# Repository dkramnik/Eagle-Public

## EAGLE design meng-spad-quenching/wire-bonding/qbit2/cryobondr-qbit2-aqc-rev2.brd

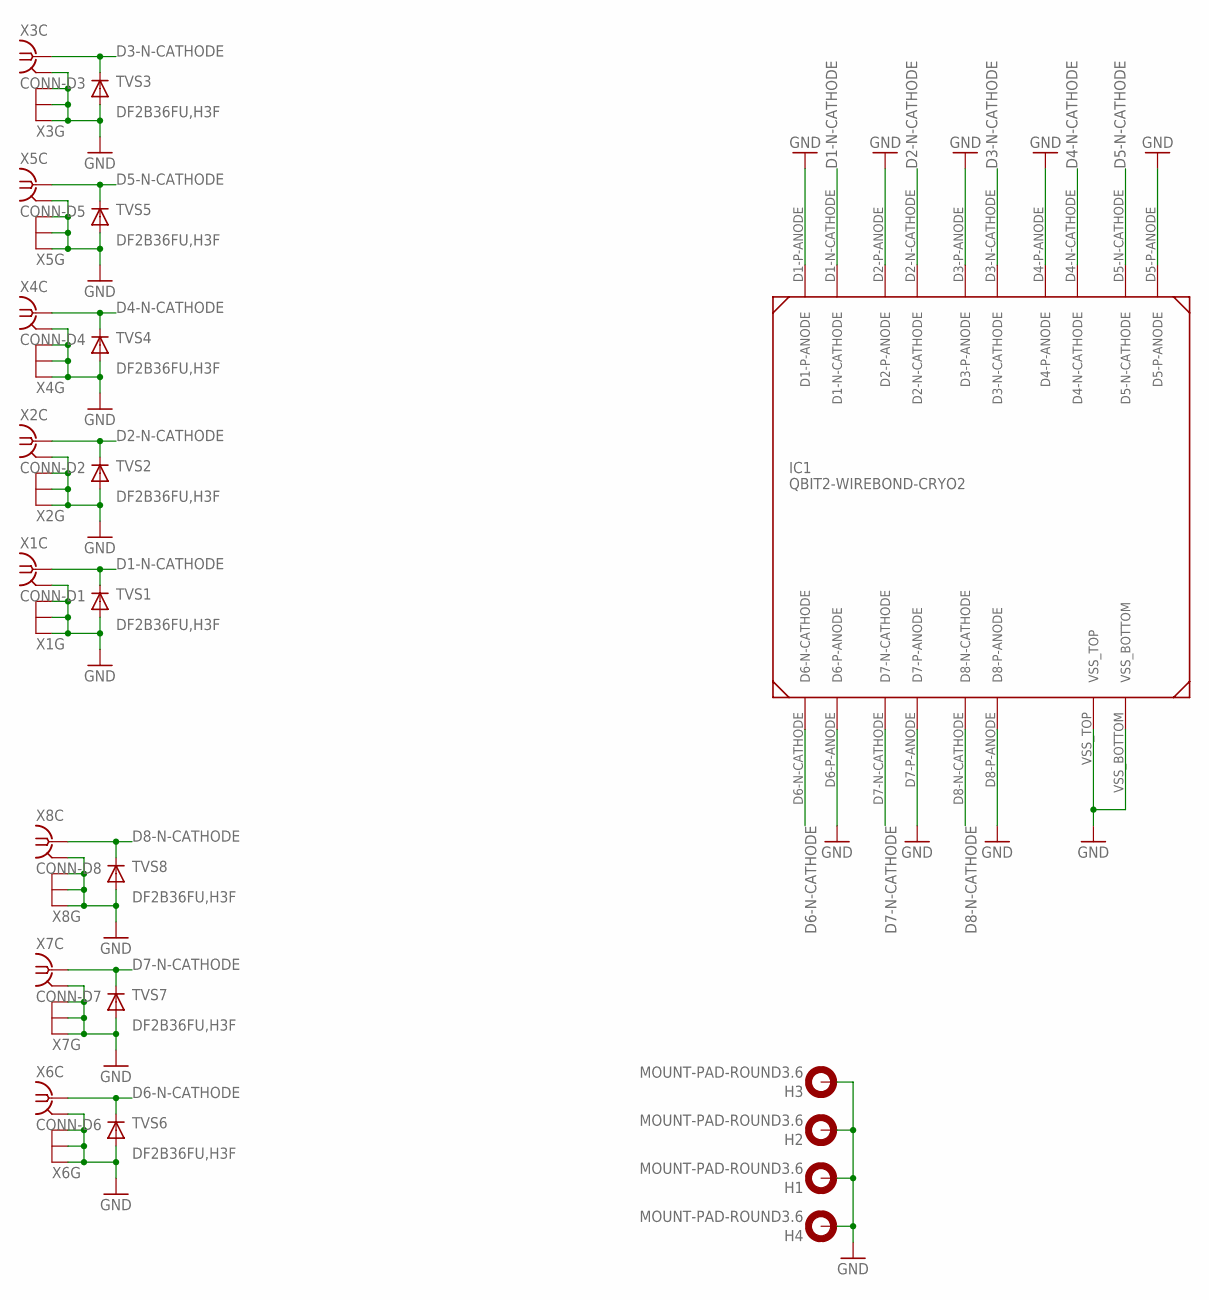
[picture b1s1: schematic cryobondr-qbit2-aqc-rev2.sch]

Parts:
H1, H2, H3, H4: MOUNT-PAD-ROUND3.6; 3,6-PAD
IC1: QBIT2-WIREBOND-CRYO2
TVS1, TVS2, TVS3, TVS4, TVS5, TVS6, TVS7, TVS8: DF2B36FU,H3F; SOD323-R
X1: CONN-D1; MMCX-SMT-BIGPADS
X2: CONN-D2; MMCX-SMT-BIGPADS
X3: CONN-D3; MMCX-SMT-BIGPADS
X4: CONN-D4; MMCX-SMT-BIGPADS
X5: CONN-D5; MMCX-SMT-BIGPADS
X6: CONN-D6; MMCX-SMT-BIGPADS
X7: CONN-D7; MMCX-SMT-BIGPADS
X8: CONN-D8; MMCX-SMT-BIGPADS

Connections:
D1-N-CATHODE: IC1.D1-N-CATHODE, TVS1.C, X1.S (1)
D2-N-CATHODE: IC1.D2-N-CATHODE, TVS2.C, X2.S (1)
D3-N-CATHODE: IC1.D3-N-CATHODE, TVS3.C, X3.S (1)
D4-N-CATHODE: IC1.D4-N-CATHODE, TVS4.C, X4.S (1)
D5-N-CATHODE: IC1.D5-N-CATHODE, TVS5.C, X5.S (1)
D6-N-CATHODE: IC1.D6-N-CATHODE, TVS6.C, X6.S (1)
D7-N-CATHODE: IC1.D7-N-CATHODE, TVS7.C, X7.S (1)
D8-N-CATHODE: IC1.D8-N-CATHODE, TVS8.C, X8.S (1)
GND: H1.B3,6, H2.B3,6, H3.B3,6, H4.B3,6, IC1.D1-P-ANODE, IC1.D2-P-ANODE, IC1.D3-P-ANODE, IC1.D4-P-ANODE, IC1.D5-P-ANODE, IC1.D6-P-ANODE, IC1.D7-P-ANODE, IC1.D8-P-ANODE, IC1.VSS_BOTTOM, IC1.VSS_TOP, TVS1.A, TVS2.A, TVS3.A, TVS4.A, TVS5.A, TVS6.A, TVS7.A, TVS8.A, X1.G1 (GND), X1.G2 (GND), X1.G3 (GND), X1.G4 (GND), X2.G1 (GND), X2.G2 (GND), X2.G3 (GND), X2.G4 (GND), X3.G1 (GND), X3.G2 (GND), X3.G3 (GND), X3.G4 (GND), X4.G1 (GND), X4.G2 (GND), X4.G3 (GND), X4.G4 (GND), X5.G1 (GND), X5.G2 (GND), X5.G3 (GND), X5.G4 (GND), X6.G1 (GND), X6.G2 (GND), X6.G3 (GND), X6.G4 (GND), X7.G1 (GND), X7.G2 (GND), X7.G3 (GND), X7.G4 (GND), X8.G1 (GND), X8.G2 (GND), X8.G3 (GND), X8.G4 (GND)

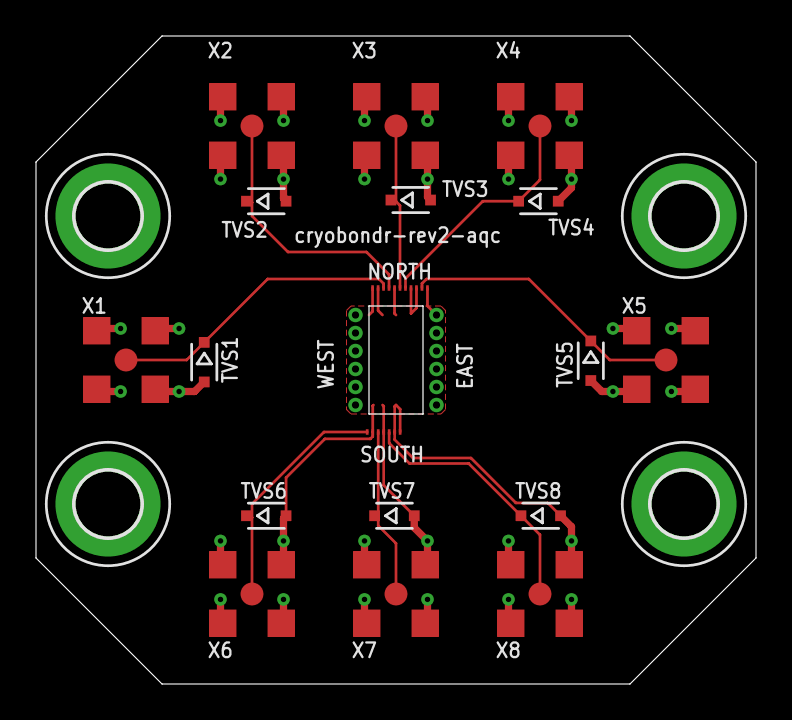
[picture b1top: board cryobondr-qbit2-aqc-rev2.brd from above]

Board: 2 copper layers, 40.0 x 36.0 mm, 21 parts (0 on the bottom side), 9 nets.

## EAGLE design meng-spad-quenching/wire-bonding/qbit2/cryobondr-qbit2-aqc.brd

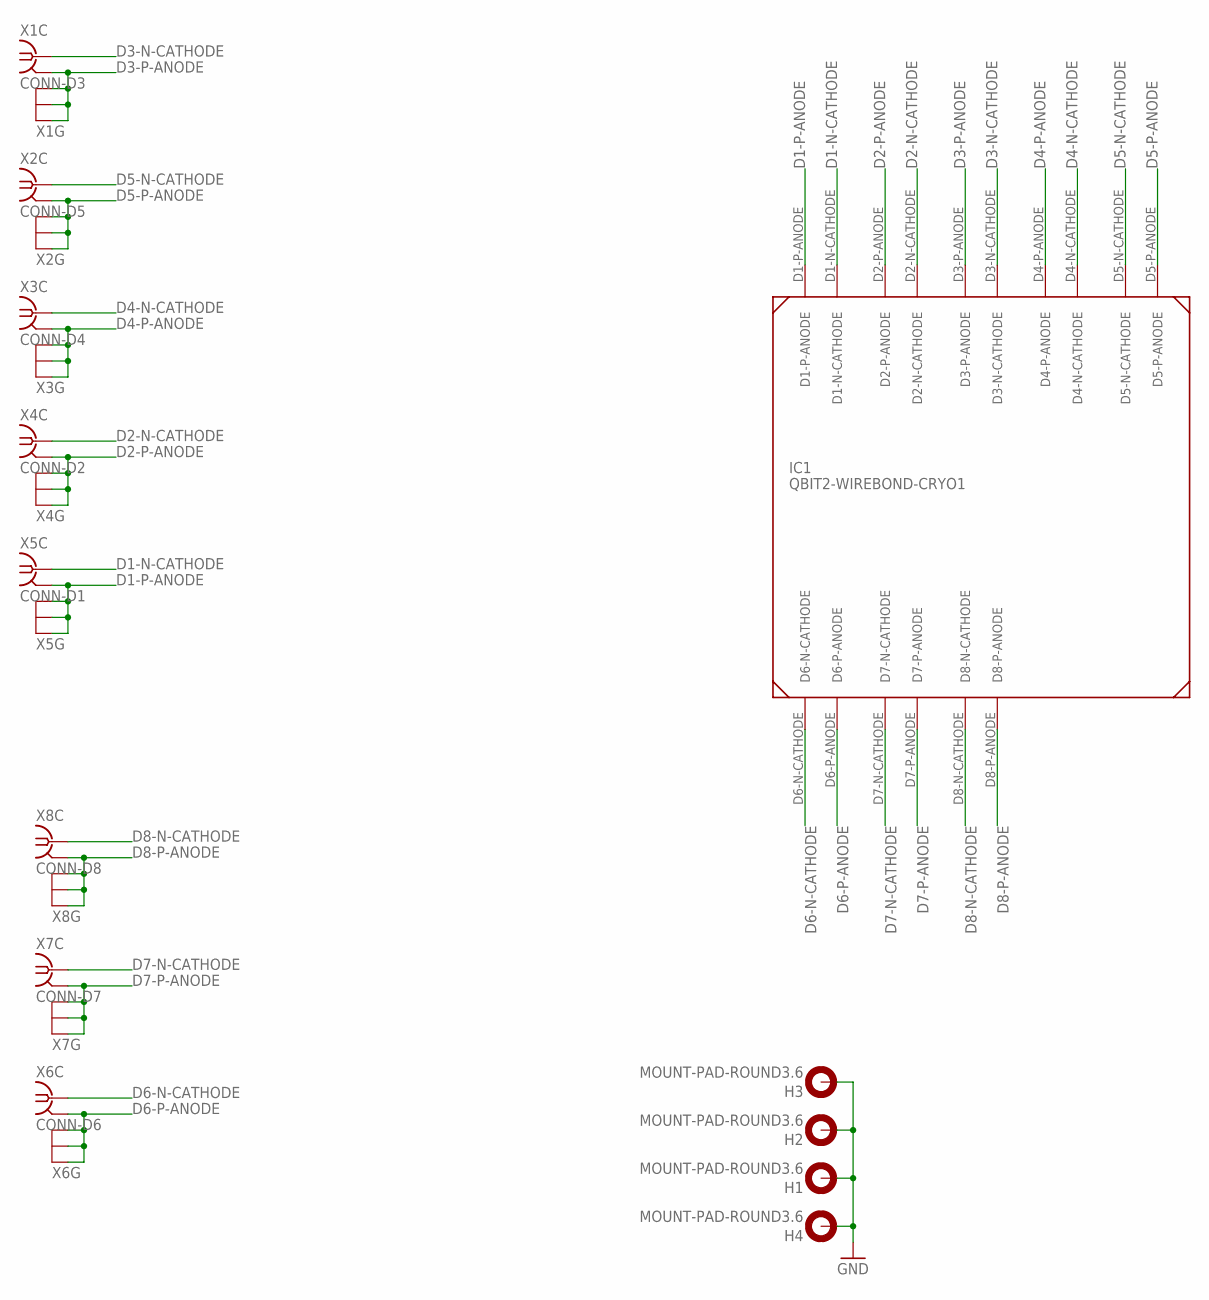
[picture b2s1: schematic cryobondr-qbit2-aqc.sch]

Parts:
H1, H2, H3, H4: MOUNT-PAD-ROUND3.6; 3,6-PAD
IC1: QBIT2-WIREBOND-CRYO1
X1: CONN-D3; MMCX-SMT
X2: CONN-D5; MMCX-SMT
X3: CONN-D4; MMCX-SMT
X4: CONN-D2; MMCX-SMT
X5: CONN-D1; MMCX-SMT
X6: CONN-D6; MMCX-SMT
X7: CONN-D7; MMCX-SMT
X8: CONN-D8; MMCX-SMT

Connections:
D1-N-CATHODE: IC1.D1-N-CATHODE, X5.S (1)
D1-P-ANODE: IC1.D1-P-ANODE, X5.G1 (GND), X5.G2 (GND), X5.G3 (GND), X5.G4 (GND)
D2-N-CATHODE: IC1.D2-N-CATHODE, X4.S (1)
D2-P-ANODE: IC1.D2-P-ANODE, X4.G1 (GND), X4.G2 (GND), X4.G3 (GND), X4.G4 (GND)
D3-N-CATHODE: IC1.D3-N-CATHODE, X1.S (1)
D3-P-ANODE: IC1.D3-P-ANODE, X1.G1 (GND), X1.G2 (GND), X1.G3 (GND), X1.G4 (GND)
D4-N-CATHODE: IC1.D4-N-CATHODE, X3.S (1)
D4-P-ANODE: IC1.D4-P-ANODE, X3.G1 (GND), X3.G2 (GND), X3.G3 (GND), X3.G4 (GND)
D5-N-CATHODE: IC1.D5-N-CATHODE, X2.S (1)
D5-P-ANODE: IC1.D5-P-ANODE, X2.G1 (GND), X2.G2 (GND), X2.G3 (GND), X2.G4 (GND)
D6-N-CATHODE: IC1.D6-N-CATHODE, X6.S (1)
D6-P-ANODE: IC1.D6-P-ANODE, X6.G1 (GND), X6.G2 (GND), X6.G3 (GND), X6.G4 (GND)
D7-N-CATHODE: IC1.D7-N-CATHODE, X7.S (1)
D7-P-ANODE: IC1.D7-P-ANODE, X7.G1 (GND), X7.G2 (GND), X7.G3 (GND), X7.G4 (GND)
D8-N-CATHODE: IC1.D8-N-CATHODE, X8.S (1)
D8-P-ANODE: IC1.D8-P-ANODE, X8.G1 (GND), X8.G2 (GND), X8.G3 (GND), X8.G4 (GND)
GND: H1.B3,6, H2.B3,6, H3.B3,6, H4.B3,6

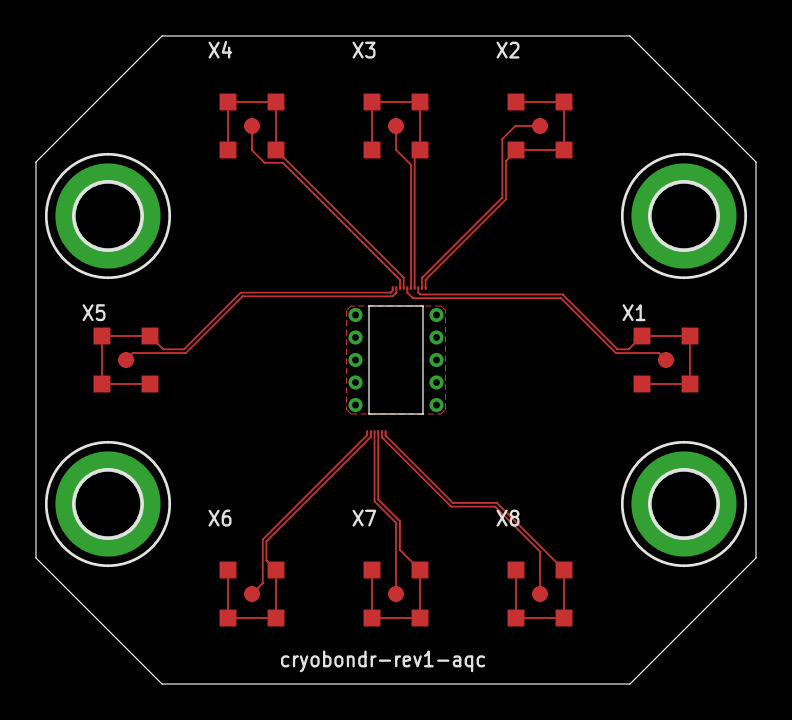
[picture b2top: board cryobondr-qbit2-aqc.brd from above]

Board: 2 copper layers, 40.0 x 36.0 mm, 13 parts (0 on the bottom side), 17 nets.

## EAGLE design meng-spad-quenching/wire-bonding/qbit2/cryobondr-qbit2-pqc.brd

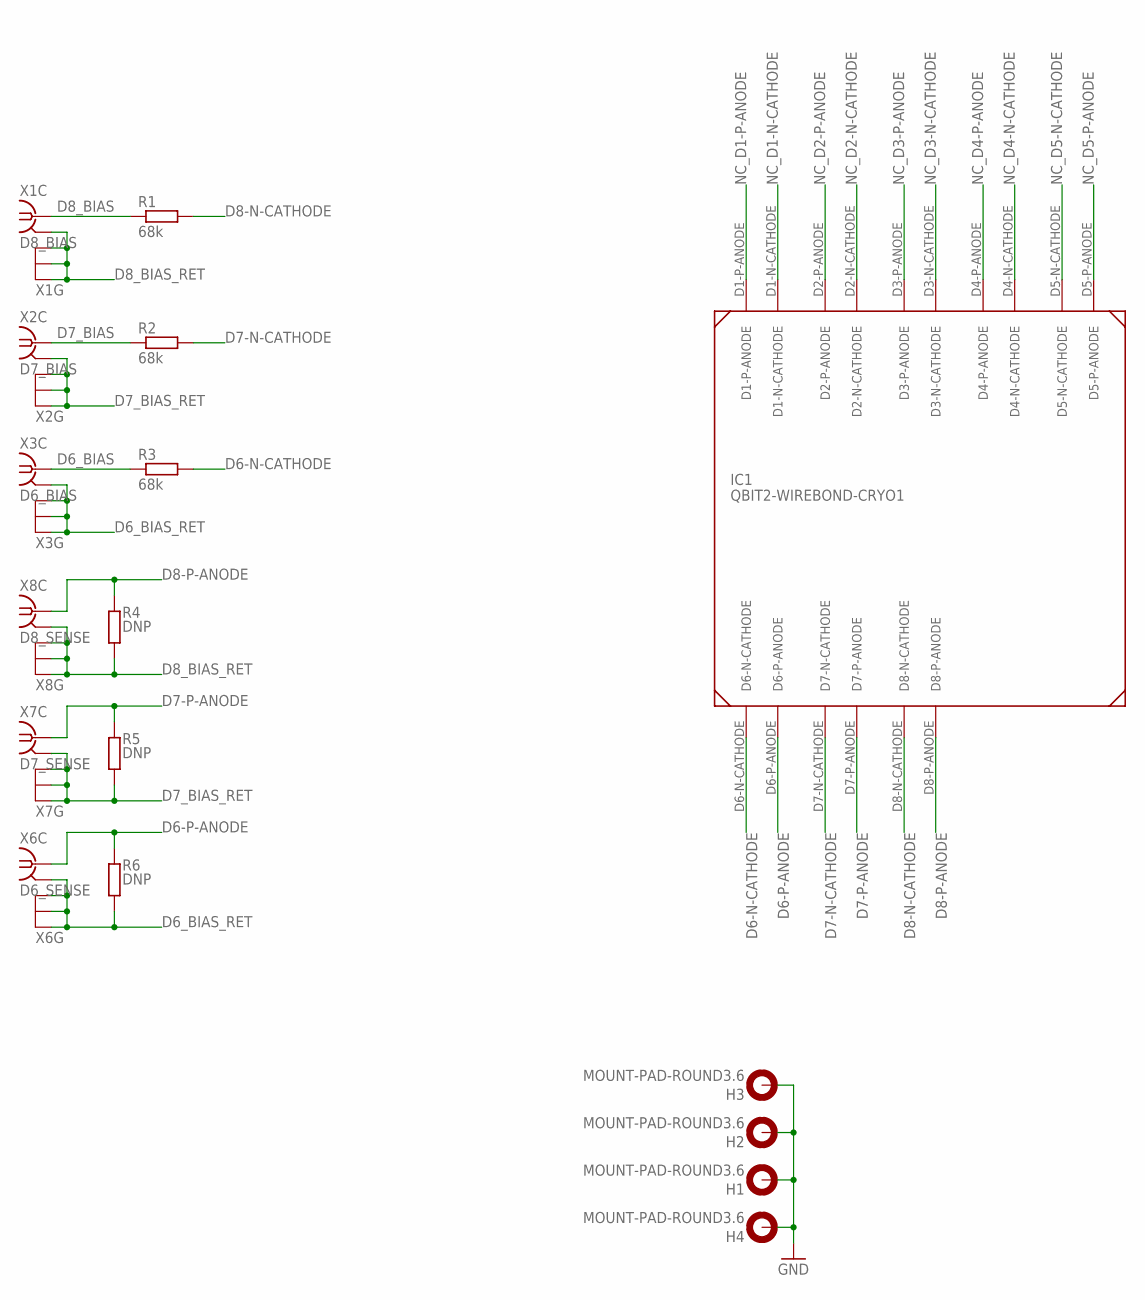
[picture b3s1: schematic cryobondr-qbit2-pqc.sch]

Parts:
H1, H2, H3, H4: MOUNT-PAD-ROUND3.6; 3,6-PAD
IC1: QBIT2-WIREBOND-CRYO1
R1, R2, R3: 68k; R0603
R4, R5, R6: DNP; R0603
X1: D8_BIAS; MMCX-SMT
X2: D7_BIAS; MMCX-SMT
X3: D6_BIAS; MMCX-SMT
X6: D6_SENSE; MMCX-SMT
X7: D7_SENSE; MMCX-SMT
X8: D8_SENSE; MMCX-SMT

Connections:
D6-N-CATHODE: IC1.D6-N-CATHODE, R3.2
D6-P-ANODE: IC1.D6-P-ANODE, R6.1, X6.S (1)
D6_BIAS: R3.1, X3.S (1)
D6_BIAS_RET: R6.2, X3.G1 (GND), X3.G2 (GND), X3.G3 (GND), X3.G4 (GND), X6.G1 (GND), X6.G2 (GND), X6.G3 (GND), X6.G4 (GND)
D7-N-CATHODE: IC1.D7-N-CATHODE, R2.2
D7-P-ANODE: IC1.D7-P-ANODE, R5.1, X7.S (1)
D7_BIAS: R2.1, X2.S (1)
D7_BIAS_RET: R5.2, X2.G1 (GND), X2.G2 (GND), X2.G3 (GND), X2.G4 (GND), X7.G1 (GND), X7.G2 (GND), X7.G3 (GND), X7.G4 (GND)
D8-N-CATHODE: IC1.D8-N-CATHODE, R1.2
D8-P-ANODE: IC1.D8-P-ANODE, R4.1, X8.S (1)
D8_BIAS: R1.1, X1.S (1)
D8_BIAS_RET: R4.2, X1.G1 (GND), X1.G2 (GND), X1.G3 (GND), X1.G4 (GND), X8.G1 (GND), X8.G2 (GND), X8.G3 (GND), X8.G4 (GND)
GND: H1.B3,6, H2.B3,6, H3.B3,6, H4.B3,6
NC_D1-N-CATHODE: IC1.D1-N-CATHODE
NC_D1-P-ANODE: IC1.D1-P-ANODE
NC_D2-N-CATHODE: IC1.D2-N-CATHODE
NC_D2-P-ANODE: IC1.D2-P-ANODE
NC_D3-N-CATHODE: IC1.D3-N-CATHODE
NC_D3-P-ANODE: IC1.D3-P-ANODE
NC_D4-N-CATHODE: IC1.D4-N-CATHODE
NC_D4-P-ANODE: IC1.D4-P-ANODE
NC_D5-N-CATHODE: IC1.D5-N-CATHODE
NC_D5-P-ANODE: IC1.D5-P-ANODE

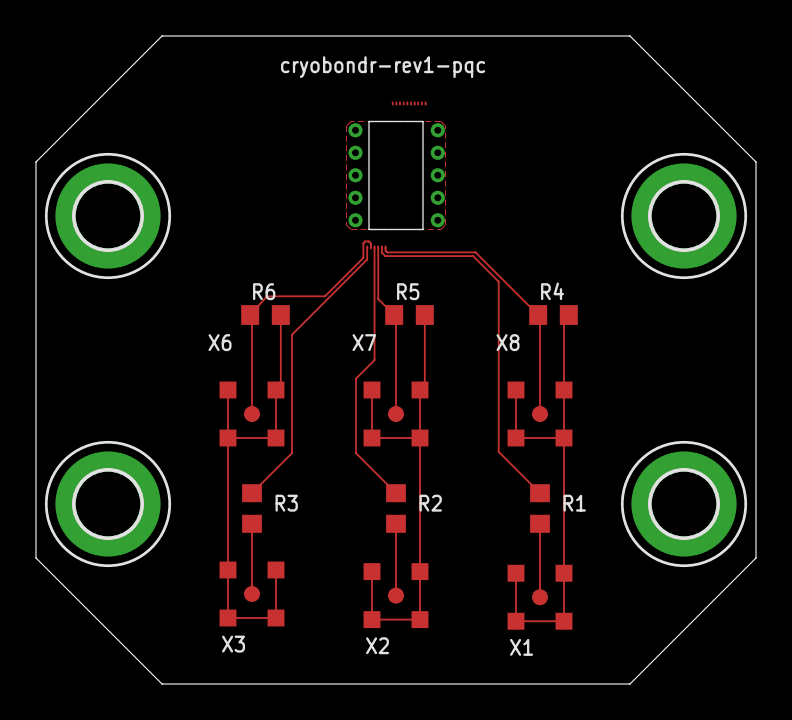
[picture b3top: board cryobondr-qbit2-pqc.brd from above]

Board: 2 copper layers, 40.0 x 36.0 mm, 17 parts (0 on the bottom side), 13 nets.

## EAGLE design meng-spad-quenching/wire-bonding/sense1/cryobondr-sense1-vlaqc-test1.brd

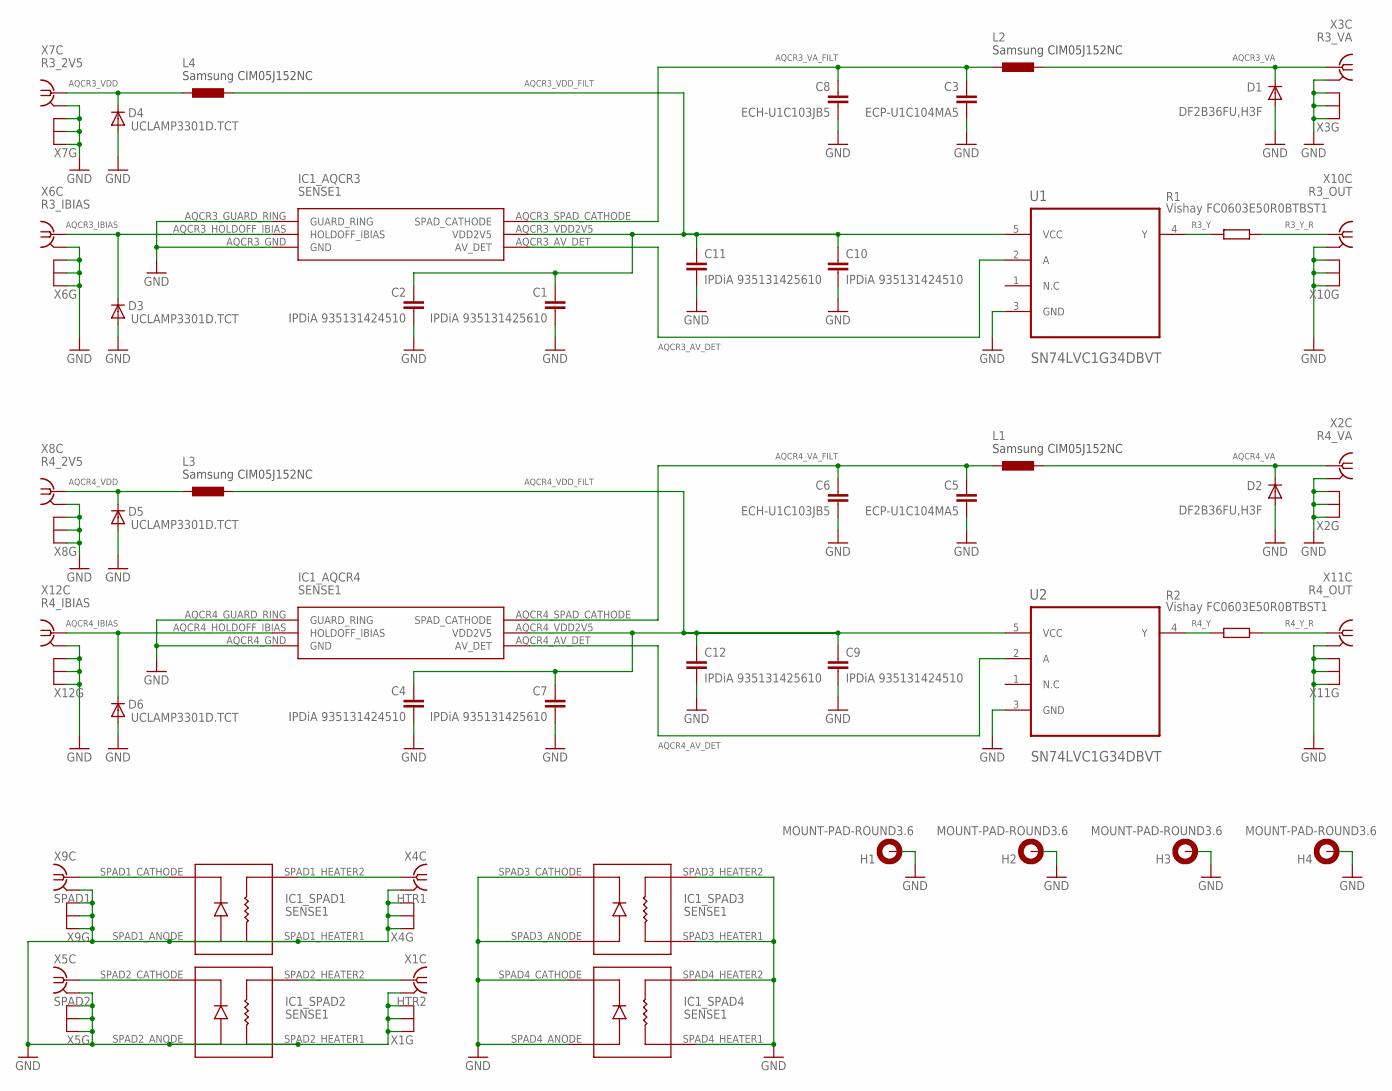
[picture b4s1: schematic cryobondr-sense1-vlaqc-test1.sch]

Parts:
C1, C7, C11, C12: IPDiA 935131425610; C0603
C2, C4, C9, C10: IPDiA 935131424510; C0402
C3, C5: ECP-U1C104MA5; C0805
C6, C8: ECH-U1C103JB5; C0805
D1, D2: DF2B36FU,H3F; SOD323-W
D3, D4, D5, D6: UCLAMP3301D.TCT; SOD323-W
H1, H2, H3, H4: MOUNT-PAD-ROUND3.6; 3,6-PAD
IC1: SENSE1; SENSE1-WIREBOND-VLAQC-TEST1
L1, L2, L3, L4: Samsung CIM05J152NC; R0402
R1, R2: Vishay FC0603E50R0BTBST1; R0603
U1, U2: SN74LVC1G34DBVT; SOT95P280X145-5N
X1: HTR2; MMCX-SMT-BIGPADS
X2: R4_VA; MMCX-SMT-BIGPADS
X3: R3_VA; MMCX-SMT-BIGPADS
X4: HTR1; MMCX-SMT-BIGPADS
X5: SPAD2; MMCX-SMT-BIGPADS
X6: R3_IBIAS; MMCX-SMT-BIGPADS
X7: R3_2V5; MMCX-SMT-BIGPADS
X8: R4_2V5; MMCX-SMT-BIGPADS
X9: SPAD1; MMCX-SMT-BIGPADS
X10: R3_OUT; MMCX-SMT-BIGPADS
X11: R4_OUT; MMCX-SMT-BIGPADS
X12: R4_IBIAS; MMCX-SMT-BIGPADS

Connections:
AQCR3_AV_DET: IC1.AQCR3_AV_DET (AV_DET), U1.2 (A)
AQCR3_IBIAS: D3.C, IC1.AQCR3_HOLDOFF_IBIAS (HOLDOFF_IBIAS), X6.S (1)
AQCR3_VA: D1.C, L2.2, X3.S (1)
AQCR3_VA_FILT: C3.1, C8.1, IC1.AQCR3_SPAD_CATHODE (SPAD_CATHODE), L2.1
AQCR3_VDD: D4.C, L4.1, X7.S (1)
AQCR3_VDD_FILT: C1.1, C2.1, C10.1, C11.1, IC1.AQCR3_VDD2V5 (VDD2V5), L4.2, U1.5 (VCC)
AQCR4_AV_DET: IC1.AQCR4_AV_DET (AV_DET), U2.2 (A)
AQCR4_IBIAS: D6.C, IC1.AQCR4_HOLDOFF_IBIAS (HOLDOFF_IBIAS), X12.S (1)
AQCR4_VA: D2.C, L1.2, X2.S (1)
AQCR4_VA_FILT: C5.1, C6.1, IC1.AQCR4_SPAD_CATHODE (SPAD_CATHODE), L1.1
AQCR4_VDD: D5.C, L3.1, X8.S (1)
AQCR4_VDD_FILT: C4.1, C7.1, C9.1, C12.1, IC1.AQCR4_VDD2V5 (VDD2V5), L3.2, U2.5 (VCC)
GND: C1.2, C2.2, C3.2, C4.2, C5.2, C6.2, C7.2, C8.2, C9.2, C10.2, C11.2, C12.2, D1.A, D2.A, D3.A, D4.A, D5.A, D6.A, H1.B3,6, H2.B3,6, H3.B3,6, H4.B3,6, IC1.AQCR3_GND (GND), IC1.AQCR3_GUARD_RING (GUARD_RING), IC1.AQCR4_GND (GND), IC1.AQCR4_GUARD_RING (GUARD_RING), IC1.SPAD1_ANODE (SPAD_ANODE), IC1.SPAD1_HEATER1 (SPAD_HEATER1), IC1.SPAD2_ANODE (SPAD_ANODE), IC1.SPAD2_HEATER1 (SPAD_HEATER1), IC1.SPAD3_ANODE (SPAD_ANODE), IC1.SPAD3_CATHODE (SPAD_CATHODE), IC1.SPAD3_HEATER1 (SPAD_HEATER1), IC1.SPAD3_HEATER2 (SPAD_HEATER2), IC1.SPAD4_ANODE (SPAD_ANODE), IC1.SPAD4_CATHODE (SPAD_CATHODE), IC1.SPAD4_HEATER1 (SPAD_HEATER1), IC1.SPAD4_HEATER2 (SPAD_HEATER2), U1.3 (GND), U2.3 (GND), X1.G1 (GND), X1.G2 (GND), X1.G3 (GND), X1.G4 (GND), X2.G1 (GND), X2.G2 (GND), X2.G3 (GND), X2.G4 (GND), X3.G1 (GND), X3.G2 (GND), X3.G3 (GND), X3.G4 (GND), X4.G1 (GND), X4.G2 (GND), X4.G3 (GND), X4.G4 (GND), X5.G1 (GND), X5.G2 (GND), X5.G3 (GND), X5.G4 (GND), X6.G1 (GND), X6.G2 (GND), X6.G3 (GND), X6.G4 (GND), X7.G1 (GND), X7.G2 (GND), X7.G3 (GND), X7.G4 (GND), X8.G1 (GND), X8.G2 (GND), X8.G3 (GND), X8.G4 (GND), X9.G1 (GND), X9.G2 (GND), X9.G3 (GND), X9.G4 (GND), X10.G1 (GND), X10.G2 (GND), X10.G3 (GND), X10.G4 (GND), X11.G1 (GND), X11.G2 (GND), X11.G3 (GND), X11.G4 (GND), X12.G1 (GND), X12.G2 (GND), X12.G3 (GND), X12.G4 (GND)
R3_Y: R1.1, U1.4 (Y)
R3_Y_R: R1.2, X10.S (1)
R4_Y: R2.1, U2.4 (Y)
R4_Y_R: R2.2, X11.S (1)
SPAD1_CATH: IC1.SPAD1_CATHODE (SPAD_CATHODE), X9.S (1)
SPAD1_HTR: IC1.SPAD1_HEATER2 (SPAD_HEATER2), X4.S (1)
SPAD2_CATH: IC1.SPAD2_CATHODE (SPAD_CATHODE), X5.S (1)
SPAD2_HTR: IC1.SPAD2_HEATER2 (SPAD_HEATER2), X1.S (1)

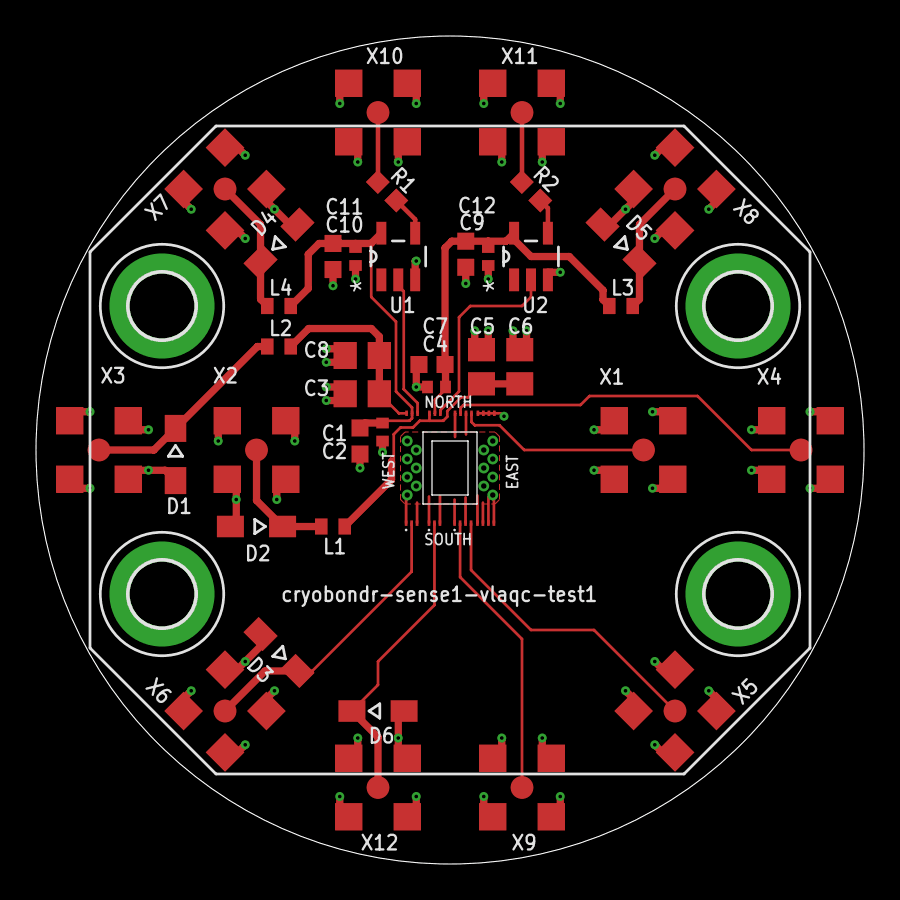
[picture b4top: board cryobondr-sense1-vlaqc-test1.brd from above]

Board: 2 copper layers, 46.0 x 46.0 mm, 43 parts (0 on the bottom side), 21 nets.

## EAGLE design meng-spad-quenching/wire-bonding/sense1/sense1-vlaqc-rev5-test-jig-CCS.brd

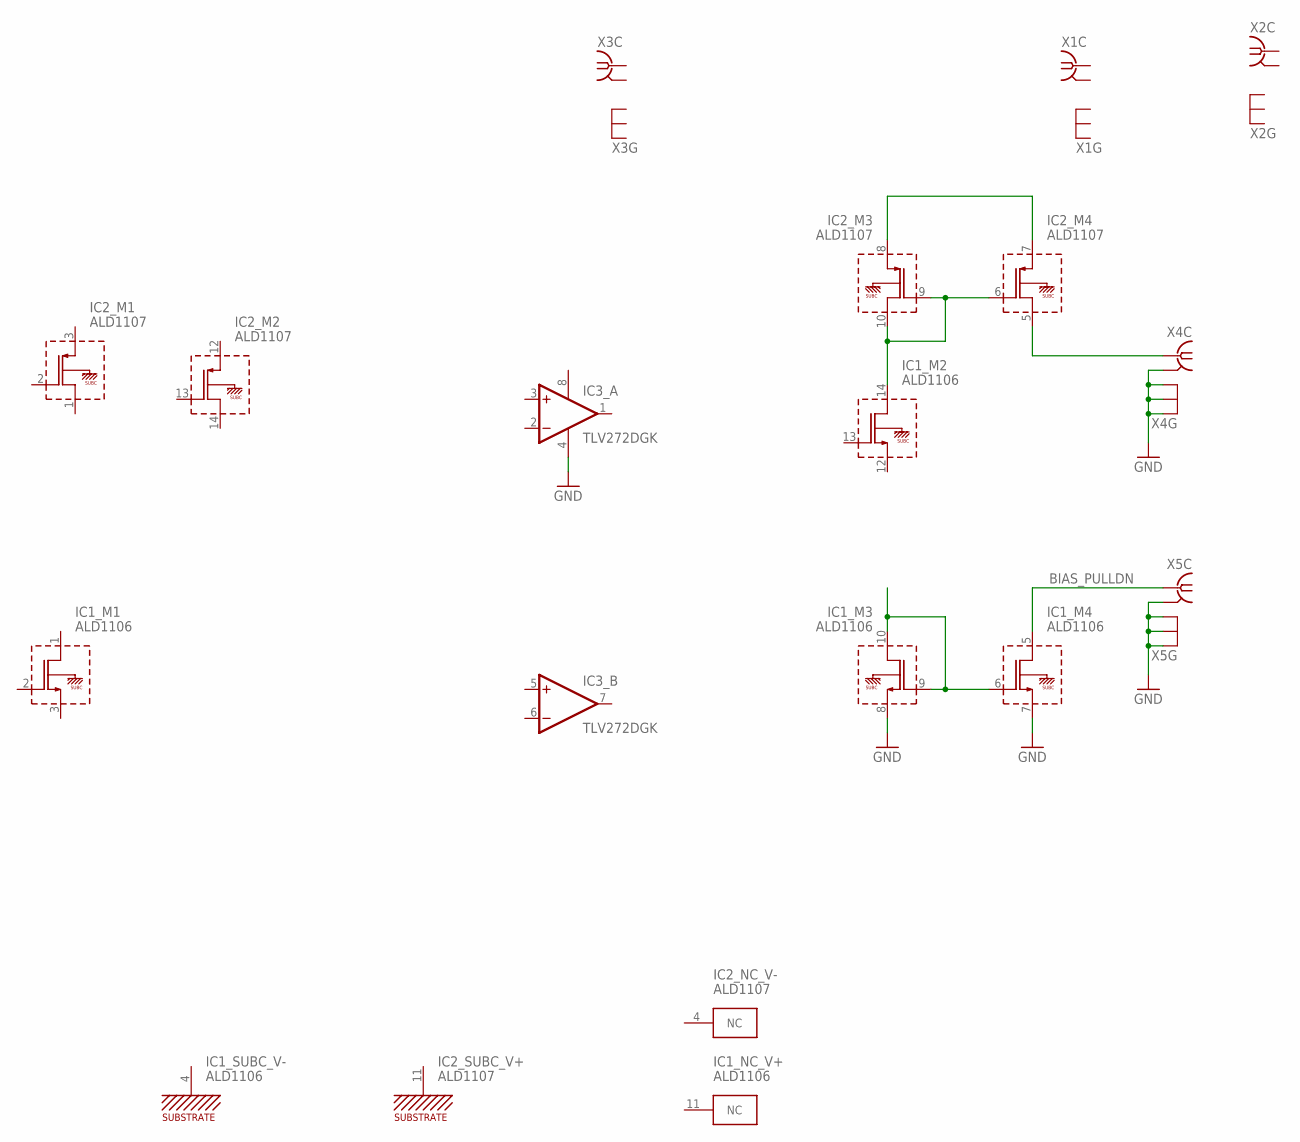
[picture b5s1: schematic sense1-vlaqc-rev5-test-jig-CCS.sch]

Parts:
IC1: ALD1106; SO14
IC2: ALD1107; SO14
IC3: TLV272DGK; MSOP8
X1, X2, X3, X4, X5: MMCXBIGPAD; MMCX-SMT-BIGPADS

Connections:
BIAS_PULLDN: IC1.5 (D), X5.S (1)
GND: IC1.7 (S), IC1.8 (S), IC3.4 (V-), X1.G1 (GND), X1.G2 (GND), X1.G3 (GND), X1.G4 (GND), X2.G1 (GND), X2.G2 (GND), X2.G3 (GND), X2.G4 (GND), X3.G1 (GND), X3.G2 (GND), X3.G3 (GND), X3.G4 (GND), X4.G1 (GND), X4.G2 (GND), X4.G3 (GND), X4.G4 (GND), X5.G1 (GND), X5.G2 (GND), X5.G3 (GND), X5.G4 (GND)
unnamed: IC2.5 (D), X4.S (1)
unnamed: IC1.14 (D), IC2.6 (G), IC2.9 (G), IC2.10 (D)
unnamed: IC1.6 (G), IC1.9 (G), IC1.10 (D)
unnamed: IC2.7 (S), IC2.8 (S)
V+: IC3.8 (V+)

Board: 2 copper layers, 8 parts (0 on the bottom side), 6 nets, no tracks yet.

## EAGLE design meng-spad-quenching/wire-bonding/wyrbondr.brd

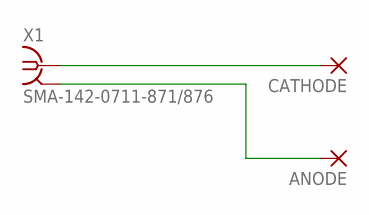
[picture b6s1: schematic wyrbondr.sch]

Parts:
ANODE: SMD2; SMD1,27-2,54
CATHODE: SMD2; SMD1,27-2,54
X1: SMA-142-0711-871/876; J502-ND-142-0711-871/876

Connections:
CATHODE: CATHODE.1, X1.1
GND: ANODE.1, X1.G@1 (GND), X1.G@2 (GND), X1.G@3 (GND), X1.G@4 (GND)

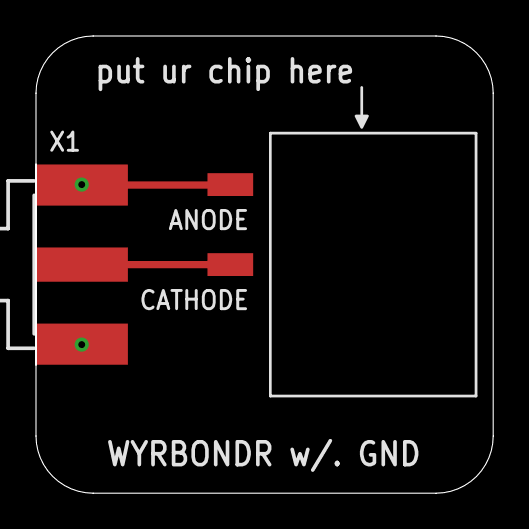
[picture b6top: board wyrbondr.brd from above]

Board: 2 copper layers, 25.4 x 25.4 mm, 3 parts (0 on the bottom side), 2 nets.
